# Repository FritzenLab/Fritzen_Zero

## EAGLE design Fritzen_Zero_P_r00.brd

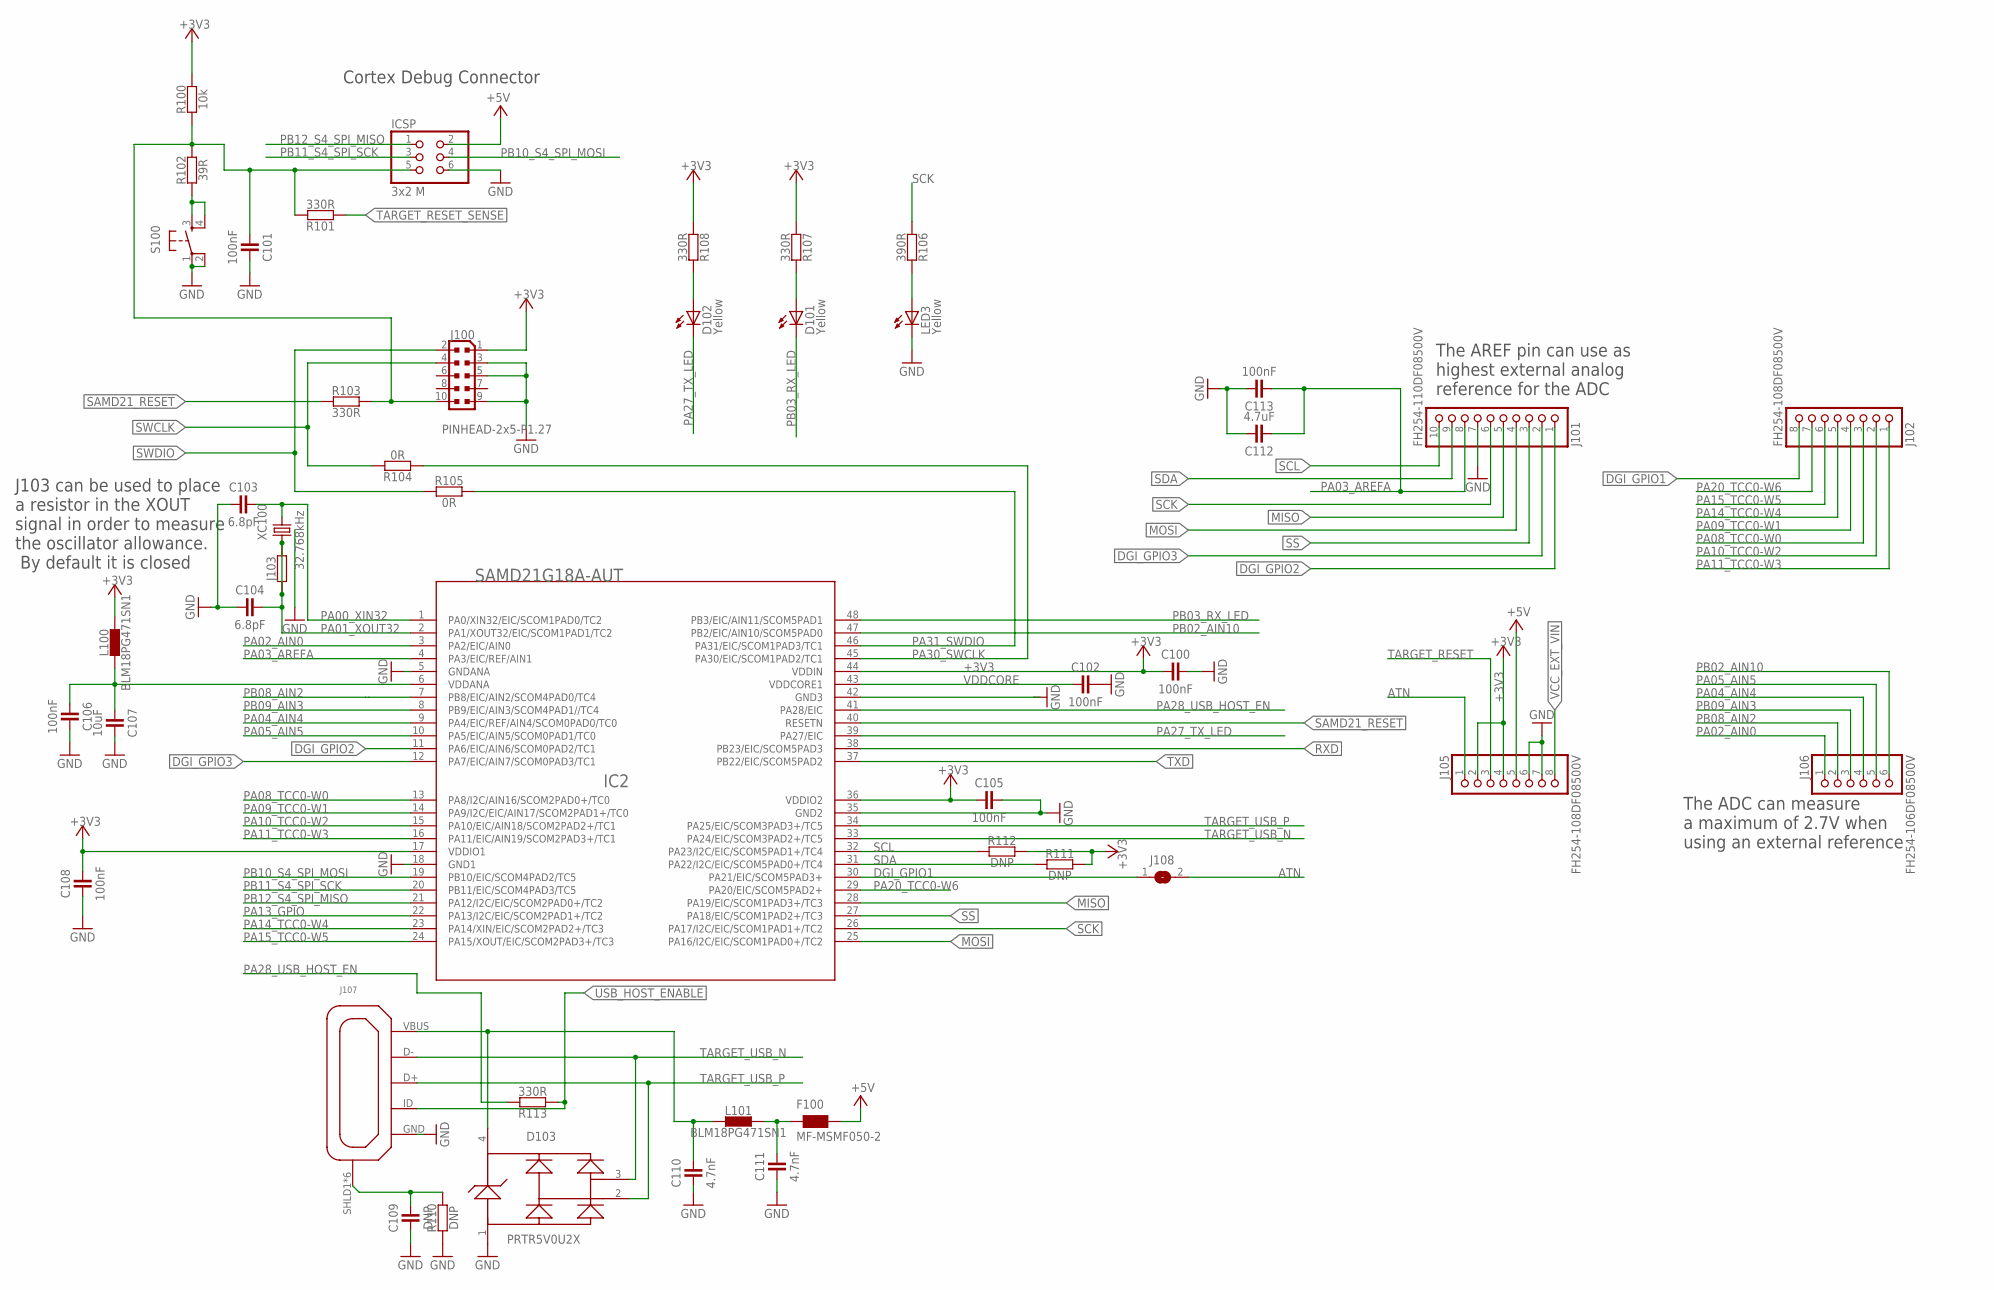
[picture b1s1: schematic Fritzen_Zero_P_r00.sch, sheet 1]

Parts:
C100, C101, C102, C105, C106, C108, C113: 100nF; C0402
C103, C104: 6.8pF; C0402
C107: 10uF; C0603
C109: DNP; C0402
C110, C111: 4.7nF; C0402
C112: 4.7uF; C0603
D101, D102: Yellow; CHIPLED_0805
D103: PRTR5V0U2XB; SOT143B
F100: MF-MSMF050-2; WUERTH-ELEKTRONIK_1812
IC2: SAMD21G18A-AUT; TQFP48
ICSP: 3x2 M; 2X03
J100: PINHEAD-2x5-P1.27; PINHEAD_2X05_127
J101: FH254-110DF08500V; 1X10
J102, J105: FH254-108DF08500V; 1X08
J103: RESISTORS-0402; C0402
J106: FH254-106DF08500V; 1X06
J107: ZX62-AB-5PA; USB-MICRO-10103594
J108: SJ
L100, L101: BLM18PG471SN1; C0603
LED3: Yellow; CHIPLED_0805
R100: 10k; C0402
R101, R103, R107, R108, R113: 330R; C0402
R102: 39R; C0402
R104, R105: 0R; C0402
R106: 390R; C0402
R110, R111, R112: DNP; C0402
S100: PUSHBUTTON3; TS42_4PINS
XC100: 32.768kHz; CRYSTAL_TC26SMD

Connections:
+3V3: C100.1, C105.1, C108.2, IC2.17 (VDDIO1), IC2.36 (VDDIO2), IC2.44 (VDDIN), J100.1, J105.2, J105.4, L100.2, R100.2, R107.1, R108.1, R111.2, R112.2; also elsewhere on the board
+5V: F100.2, ICSP.2, J105.5; also elsewhere on the board
ATN: J105.1, J108.2
DGI_GPIO1: IC2.30 (PA21/EIC/SCOM5PAD3+), J102.8, J108.1
DGI_GPIO2: IC2.11 (PA6/EIC/AIN6/SCOM0PAD2/TC1), J101.1
DGI_GPIO3: IC2.12 (PA7/EIC/AIN7/SCOM0PAD3/TC1), J101.2
GND: C100.2, C101.2, C102.2, C103.1, C104.1, C105.2, C106.2, C107.2, C108.1, C109.1, C110.1, C111.1, C112.2, C113.2, D103.1, IC2.5 (GNDANA), IC2.18 (GND1), IC2.35 (GND2), IC2.42 (GND3), ICSP.6, J100.3, J100.5, J100.9, J101.7, J105.6, J105.7, J107.GND, LED3.C, R110.1, S100.1, S100.2, XC100.P$1 (GND); also elsewhere on the board
MISO: IC2.28 (PA19/EIC/SCOM1PAD3+/TC3), J101.5
MOSI: IC2.25 (PA16/I2C/EIC/SCOM1PAD0+/TC2), J101.4
unnamed: R102.1, S100.3, S100.4
unnamed: C110.2, D103.4, J107.VBUS (VUSB), L101.1
unnamed: C106.1, C107.1, IC2.6 (VDDANA), L100.1
unnamed: C109.2, J107.SHLD1 (SH), J107.SHLD2 (SH), J107.SHLD3 (SH), J107.SHLD4 (SH), J107.SHLD5 (SH), J107.SHLD6 (SH), R110.2
unnamed: C111.2, F100.1, L101.2
unnamed: D102.A, R108.2
unnamed: D101.A, R107.2
unnamed: LED3.A, R106.2
PA00_XIN32: C103.2, IC2.1 (PA0/XIN32/EIC/SCOM1PAD0/TC2), XC100.2
PA01_XOUT32: C104.2, IC2.2 (PA1/XOUT32/EIC/SCOM1PAD1/TC2), J103.1, J103.2, XC100.1
PA02_AIN0: IC2.3 (PA2/EIC/AIN0), J106.1
PA03_AREFA: C112.1, C113.1, IC2.4 (PA3/EIC/REF/AIN1), J101.8
PA04_AIN4: IC2.9 (PA4/EIC/REF/AIN4/SCOM0PAD0/TC0), J106.4
PA05_AIN5: IC2.10 (PA5/EIC/AIN5/SCOM0PAD1/TC0), J106.5
PA08_TCC0-W0: IC2.13 (PA8/I2C/AIN16/SCOM2PAD0+/TC0), J102.3
PA09_TCC0-W1: IC2.14 (PA9/I2C/EIC/AIN17/SCOM2PAD1+/TC0), J102.4
PA10_TCC0-W2: IC2.15 (PA10/EIC/AIN18/SCOM2PAD2+/TC1), J102.2
PA11_TCC0-W3: IC2.16 (PA11/EIC/AIN19/SCOM2PAD3+/TC1), J102.1
PA13_GPIO: IC2.22 (PA13/I2C/EIC/SCOM2PAD1+/TC2)
PA14_TCC0-W4: IC2.23 (PA14/XIN/EIC/SCOM2PAD2+/TC3), J102.5
PA15_TCC0-W5: IC2.24 (PA15/XOUT/EIC/SCOM2PAD3+/TC3), J102.6
PA20_TCC0-W6: IC2.29 (PA20/EIC/SCOM5PAD2+), J102.7
PA27_TX_LED: D102.C, IC2.39 (PA27/EIC)
PA28_USB_HOST_EN: IC2.41 (PA28/EIC), R113.2
PA30_SWCLK: IC2.45 (PA30/EIC/SCOM1PAD2/TC1), R104.1
PA31_SWDIO: IC2.46 (PA31/EIC/SCOM1PAD3/TC1), R105.2
PB02_AIN10: IC2.47 (PB2/EIC/AIN10/SCOM5PAD0), J106.6
PB03_RX_LED: D101.C, IC2.48 (PB3/EIC/AIN11/SCOM5PAD1)
PB08_AIN2: IC2.7 (PB8/EIC/AIN2/SCOM4PAD0/TC4), J106.2
PB09_AIN3: IC2.8 (PB9/EIC/AIN3/SCOM4PAD1//TC4), J106.3
PB10_S4_SPI_MOSI: IC2.19 (PB10/EIC/SCOM4PAD2/TC5), ICSP.4
PB11_S4_SPI_SCK: IC2.20 (PB11/EIC/SCOM4PAD3/TC5), ICSP.3
PB12_S4_SPI_MISO: IC2.21 (PA12/I2C/EIC/SCOM2PAD0+/TC2), ICSP.1
RXD: IC2.38 (PB23/EIC/SCOM5PAD3)
SAMD21_RESET: IC2.40 (RESETN), R103.1
SCK: IC2.26 (PA17/I2C/EIC/SCOM1PAD1+/TC2), J101.6, R106.1
SCL: IC2.32 (PA23/I2C/EIC/SCOM5PAD1+/TC4), J101.10, R112.1
SDA: IC2.31 (PA22/I2C/EIC/SCOM5PAD0+/TC4), J101.9, R111.1
SS: IC2.27 (PA18/EIC/SCOM1PAD2+/TC3), J101.3
SWCLK: J100.4, R104.2
SWDIO: J100.2, R105.1
TARGET_RESET: C101.1, ICSP.5, J100.10, J105.3, R100.1, R101.2, R102.2, R103.2
TARGET_RESET_SENSE: R101.1
TARGET_USB_N: D103.3, IC2.33 (PA24/EIC/SCOM3PAD2+/TC5), J107.D-
TARGET_USB_P: D103.2, IC2.34 (PA25/EIC/SCOM3PAD3+/TC5), J107.D+
TXD: IC2.37 (PB22/EIC/SCOM5PAD2)
USB_HOST_ENABLE: J107.ID, R113.1
VCC_EXT_VIN: J105.8; also elsewhere on the board
VDDCORE: C102.1, IC2.43 (VDDCORE1)

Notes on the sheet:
Cortex Debug Connector
J103 can be used to place a resistor in the XOUT signal in order to measure the oscillator allowance. By default it is closed
The ADC can measure a maximum of 2.7V when using an external reference
The AREF pin can use as highest external analog reference for the ADC

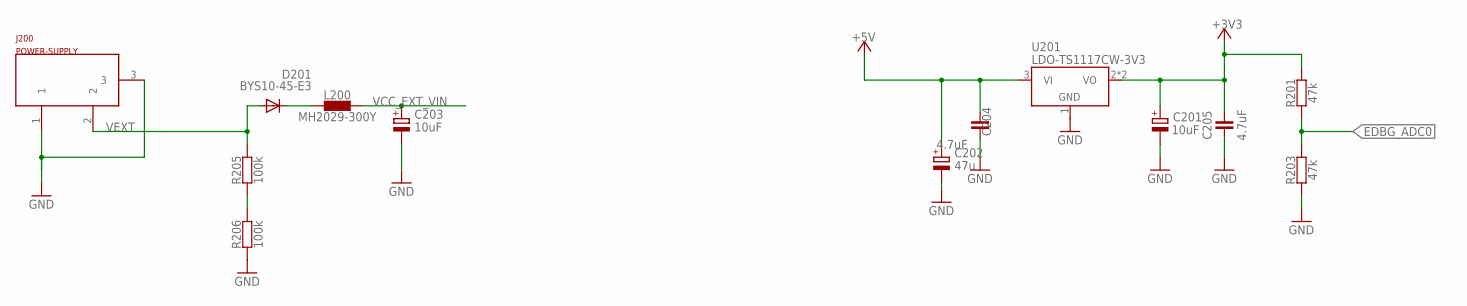
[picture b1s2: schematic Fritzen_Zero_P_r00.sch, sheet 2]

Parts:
C201, C203: 10uF; PANASONIC_D
C202: 47u; PANASONIC_D
C204, C205: 4.7uF; C0603
D201: BYS10-45-E3; MINIMELF
J200: POWER-SUPPLY; POWERSUPPLY_DC-21MM
L200: MH2029-300Y; C0805
R201, R203: 47k; C0402
R205, R206: 100k; C0402
U201: LDO-TS1117CW-3V3; SOT223

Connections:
+3V3: C201.+, C205.2, R201.2, U201.2 (VO), U201.4 (VO); also elsewhere on the board
+5V: C202.+, C204.1, U201.3 (VI); also elsewhere on the board
EDBG_ADC0: R201.1, R203.2
GND: C201.-, C202.-, C203.-, C204.2, C205.1, J200.1, J200.3, R203.1, R206.1, U201.1 (GND); also elsewhere on the board
unnamed: D201.C, L200.1
VCC_EXT_VIN: C203.+, L200.2; also elsewhere on the board
VEXT: D201.A, J200.2, R205.2
VIN_DETECT: R205.1, R206.2

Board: 2 copper layers, 59 parts (0 on the bottom side), 58 nets, no tracks yet.

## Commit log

2016-02-26 Initial release of design files
    This is an Arduino-Zero based development board. This version is based
    on the original Arduino Zero Eagle files from Arduino.cc, and features
    circuit cleaning and traces cleaning.
